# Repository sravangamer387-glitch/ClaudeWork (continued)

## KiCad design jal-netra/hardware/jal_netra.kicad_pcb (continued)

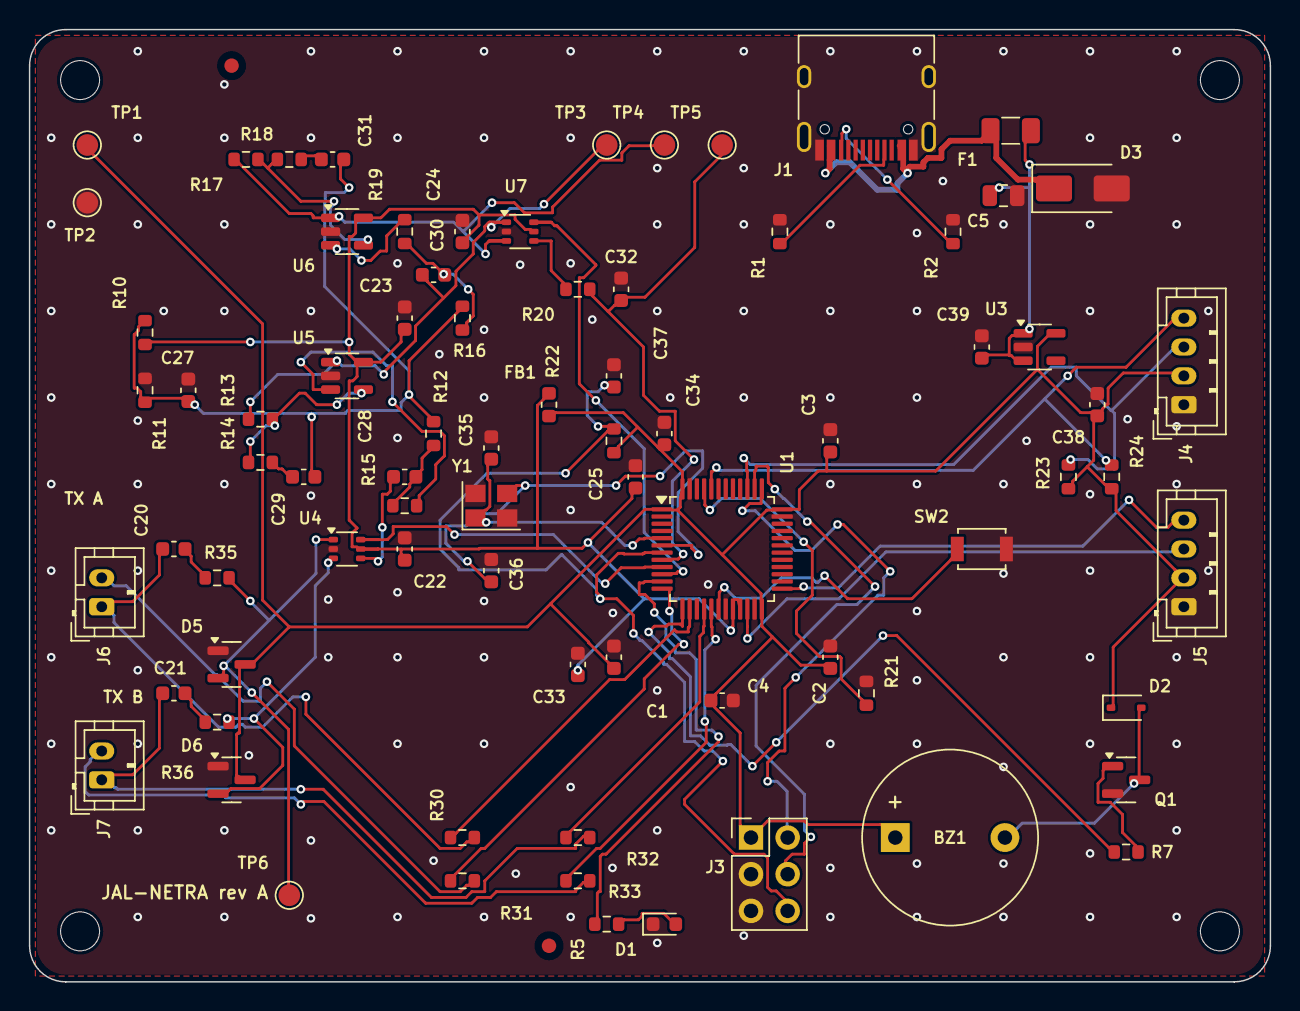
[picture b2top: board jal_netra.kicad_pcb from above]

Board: 2 copper layers, 86.0 x 66.0 mm, 84 parts (0 on the bottom side), 51 nets.

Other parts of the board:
FID1, FID2: Fiducial; Fiducial_1mm_Mask2mm
H1, H2, H3, H4: M2.5; MountingHole_2.7mm_M2.5

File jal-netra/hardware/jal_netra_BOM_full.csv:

Ref,Value,Footprint,Manufacturer part,LCSC #,LCSC status,Assembly
U1,STM32G431CBT6,Package_QFP:LQFP-48_7x7mm_P0.5mm,STM32G431CBT6,,,hand/THT
U4,TS5A3159,Package_TO_SOT_SMD:SOT-363_SC-70-6,,,,hand/THT
U5,OPA356,Package_TO_SOT_SMD:SOT-23-5,,,,hand/THT
U6,OPA356,Package_TO_SOT_SMD:SOT-23-5,,,,hand/THT
U7,TS5A3159,Package_TO_SOT_SMD:SOT-363_SC-70-6,,,,hand/THT
U3,AP2112K-3.3,Package_TO_SOT_SMD:SOT-23-5,,,,hand/THT
FB1,BLM18 600R,Inductor_SMD:L_0603_1608Metric,,,,hand/THT
Y1,8 MHz,Crystal:Crystal_SMD_3225-4Pin_3.2x2.5mm,,,,hand/THT
D5,BAV99,Package_TO_SOT_SMD:SOT-23,,,,hand/THT
D6,BAV99,Package_TO_SOT_SMD:SOT-23,,,,hand/THT
J6,Transducer A (BTL),Connector_JST:JST_PH_B2B-PH-K_1x02_P2.00mm_Vertical,,,,hand/THT
J7,Transducer B (BTL),Connector_JST:JST_PH_B2B-PH-K_1x02_P2.00mm_Vertical,,,,hand/THT
R30,22,Resistor_SMD:R_0603_1608Metric,,,,hand/THT
R31,22,Resistor_SMD:R_0603_1608Metric,,,,hand/THT
R32,22,Resistor_SMD:R_0603_1608Metric,,,,hand/THT
R33,22,Resistor_SMD:R_0603_1608Metric,,,,hand/THT
C20,10n,Capacitor_SMD:C_0603_1608Metric,0603 10nF X7R,C57112,verified,SMT (JLC)
R35,1k,Resistor_SMD:R_0603_1608Metric,0603 1k 1%,C21190,verified,SMT (JLC)
C21,10n,Capacitor_SMD:C_0603_1608Metric,0603 10nF X7R,C57112,verified,SMT (JLC)
R36,1k,Resistor_SMD:R_0603_1608Metric,0603 1k 1%,C21190,verified,SMT (JLC)
C22,100n,Capacitor_SMD:C_0603_1608Metric,0603 100nF X7R,C14663,verified,SMT (JLC)
C23,100n,Capacitor_SMD:C_0603_1608Metric,0603 100nF X7R,C14663,verified,SMT (JLC)
C24,100n,Capacitor_SMD:C_0603_1608Metric,0603 100nF X7R,C14663,verified,SMT (JLC)
C25,1u,Capacitor_SMD:C_0603_1608Metric,0603 1uF X7R,C15849,verified,SMT (JLC)
R10,10k,Resistor_SMD:R_0603_1608Metric,0603 10k 1%,C25804,verified,SMT (JLC)
R11,10k,Resistor_SMD:R_0603_1608Metric,0603 10k 1%,C25804,verified,SMT (JLC)
C27,1u,Capacitor_SMD:C_0603_1608Metric,0603 1uF X7R,C15849,verified,SMT (JLC)
C28,10n,Capacitor_SMD:C_0603_1608Metric,0603 10nF X7R,C57112,verified,SMT (JLC)
R12,100k,Resistor_SMD:R_0603_1608Metric,0603 100k 1%,C25803,verified,SMT (JLC)
R13,2.2k,Resistor_SMD:R_0603_1608Metric,0603 2.2k 1%,C4190,memory,SMT (JLC)
R14,240,Resistor_SMD:R_0603_1608Metric,,,,hand/THT
C29,1u,Capacitor_SMD:C_0603_1608Metric,0603 1uF X7R,C15849,verified,SMT (JLC)
R15,0,Resistor_SMD:R_0603_1608Metric,,,,hand/THT
C30,10n,Capacitor_SMD:C_0603_1608Metric,0603 10nF X7R,C57112,verified,SMT (JLC)
R16,100k,Resistor_SMD:R_0603_1608Metric,0603 100k 1%,C25803,verified,SMT (JLC)
R17,1k,Resistor_SMD:R_0603_1608Metric,0603 1k 1%,C21190,verified,SMT (JLC)
R18,100,Resistor_SMD:R_0603_1608Metric,,,,hand/THT
C31,1u,Capacitor_SMD:C_0603_1608Metric,0603 1uF X7R,C15849,verified,SMT (JLC)
R19,0,Resistor_SMD:R_0603_1608Metric,,,,hand/THT
R20,33,Resistor_SMD:R_0603_1608Metric,,,,hand/THT
C32,22p,Capacitor_SMD:C_0603_1608Metric,,,,hand/THT
C1,100n,Capacitor_SMD:C_0603_1608Metric,0603 100nF X7R,C14663,verified,SMT (JLC)
C2,100n,Capacitor_SMD:C_0603_1608Metric,0603 100nF X7R,C14663,verified,SMT (JLC)
C3,100n,Capacitor_SMD:C_0603_1608Metric,0603 100nF X7R,C14663,verified,SMT (JLC)
C4,100n,Capacitor_SMD:C_0603_1608Metric,0603 100nF X7R,C14663,verified,SMT (JLC)
C33,100n,Capacitor_SMD:C_0603_1608Metric,0603 100nF X7R,C14663,verified,SMT (JLC)
C34,4.7u,Capacitor_SMD:C_0603_1608Metric,,,,hand/THT
C35,15p,Capacitor_SMD:C_0603_1608Metric,,,,hand/THT
C36,15p,Capacitor_SMD:C_0603_1608Metric,,,,hand/THT
R21,10k,Resistor_SMD:R_0603_1608Metric,0603 10k 1%,C25804,verified,SMT (JLC)
R22,10k,Resistor_SMD:R_0603_1608Metric,0603 10k 1%,C25804,verified,SMT (JLC)
C37,100n,Capacitor_SMD:C_0603_1608Metric,0603 100nF X7R,C14663,verified,SMT (JLC)
C38,1u,Capacitor_SMD:C_0603_1608Metric,0603 1uF X7R,C15849,verified,SMT (JLC)
C39,1u,Capacitor_SMD:C_0603_1608Metric,0603 1uF X7R,C15849,verified,SMT (JLC)
J4,OLED I2C,Connector_JST:JST_PH_B4B-PH-K_1x04_P2.00mm_Vertical,,,,hand/THT
R23,4.7k,Resistor_SMD:R_0603_1608Metric,0603 4.7k 1%,C23162,memory,SMT (JLC)
R24,4.7k,Resistor_SMD:R_0603_1608Metric,0603 4.7k 1%,C23162,memory,SMT (JLC)
J5,UART host / BLE,Connector_JST:JST_PH_B4B-PH-K_1x04_P2.00mm_Vertical,,,,hand/THT
J3,SWD,Connector_PinHeader_2.54mm:PinHeader_2x03_P2.54mm_Vertical,,,,hand/THT
SW2,Test / zero,Button_Switch_SMD:SW_SPST_B3U-1000P,,,,hand/THT
TP1,TP,TestPoint:TestPoint_Pad_D1.5mm,,,,hand/THT
TP2,TP,TestPoint:TestPoint_Pad_D1.5mm,,,,hand/THT
TP3,TP,TestPoint:TestPoint_Pad_D1.5mm,,,,hand/THT
TP4,TP,TestPoint:TestPoint_Pad_D1.5mm,,,,hand/THT
TP5,TP,TestPoint:TestPoint_Pad_D1.5mm,,,,hand/THT
TP6,TP,TestPoint:TestPoint_Pad_D1.5mm,,,,hand/THT
J1,USB-C 5V,Connector_USB:USB_C_Receptacle_HRO_TYPE-C-31-M-12,TYPE-C-31-M-12,C165948,verified,SMT (JLC)
F1,PTC 500mA,Fuse:Fuse_1206_3216Metric,,,,hand/THT
D3,SMAJ5.0A,Diode_SMD:D_SMA,,,,hand/THT
R1,5.1k,Resistor_SMD:R_0603_1608Metric,0603 5.1k 1%,C23186,memory,SMT (JLC)
R2,5.1k,Resistor_SMD:R_0603_1608Metric,0603 5.1k 1%,C23186,memory,SMT (JLC)
C5,10u,Capacitor_SMD:C_0805_2012Metric,0805 10uF X5R,C15850,memory,SMT (JLC)
BZ1,Buzzer,Buzzer_Beeper:Buzzer_12x9.5RM7.6,,,,hand/THT
Q1,MMBT3904,Package_TO_SOT_SMD:SOT-23,MMBT3904,C20526,verified,SMT (JLC)
D2,1N4148WS,Diode_SMD:D_SOD-323,1N4148WS,C2128,verified,SMT (JLC)
R7,1k,Resistor_SMD:R_0603_1608Metric,0603 1k 1%,C21190,verified,SMT (JLC)
D1,Green,LED_SMD:LED_0603_1608Metric,,,,hand/THT
R5,1k,Resistor_SMD:R_0603_1608Metric,0603 1k 1%,C21190,verified,SMT (JLC)

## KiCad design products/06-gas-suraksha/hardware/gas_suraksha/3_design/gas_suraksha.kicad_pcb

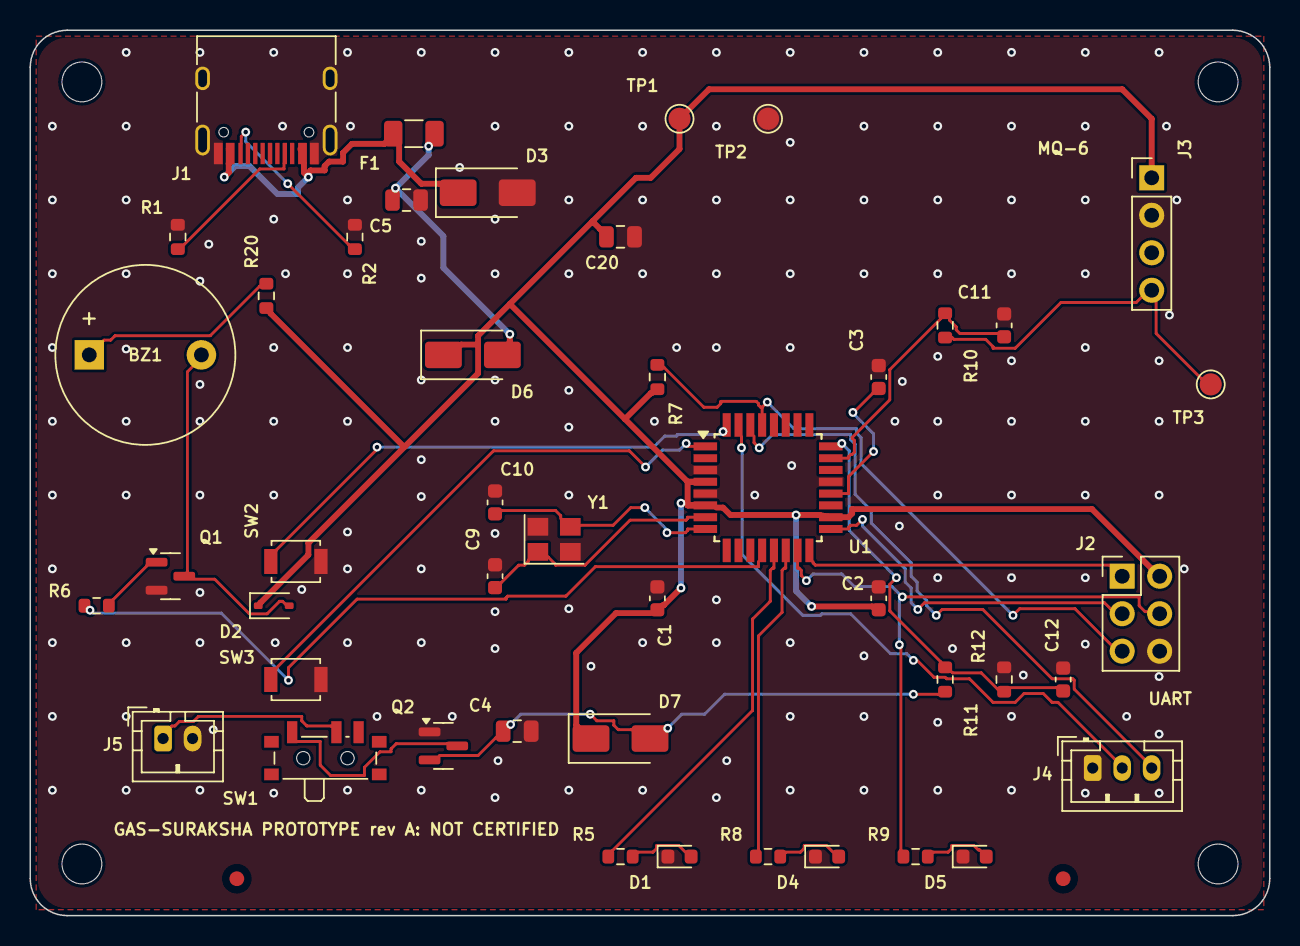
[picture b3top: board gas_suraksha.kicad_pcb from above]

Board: 2 copper layers, 84.0 x 60.0 mm, 51 parts (0 on the bottom side), 32 nets.

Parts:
BZ1: Buzzer active 3V; Buzzer_12x9.5RM7.6
C1, C2, C3, C11, C12: 100n; C_0603_1608Metric
C4, C5, C20: 10u; C_0805_2012Metric
C9, C10: 22p; C_0603_1608Metric
D1: Green; LED_0603_1608Metric
D2: 1N4148WS; D_SOD-323
D3: SMAJ5.0A; D_SMA
D4: Amber; LED_0603_1608Metric
D5: Red; LED_0603_1608Metric
D6, D7: SS14; D_SMA
F1: PTC 500mA; Fuse_1206_3216Metric
FID1, FID2: Fiducial; Fiducial_1mm_Mask2mm
H1, H2, H3, H4: M2.5; MountingHole_2.7mm_M2.5
J1: USB-C 5V; USB_C_Receptacle_HRO_TYPE-C-31-M-12
J2: ISP; PinHeader_2x03_P2.54mm_Vertical
J3: MQ-6 module: VCC GND DO AO; PinHeader_1x04_P2.54mm_Vertical
J4: UART log (adapter RX, TX); JST_PH_B3B-PH-K_1x03_P2.00mm_Vertical
J5: BATT 3xAA; JST_PH_B2B-PH-K_1x02_P2.00mm_Vertical
Q1: MMBT3904; SOT-23
Q2: AO3401A; SOT-23
R1, R2: 5.1k; R_0603_1608Metric
R5, R6, R8, R9, R10: 1k; R_0603_1608Metric
R7: 10k; R_0603_1608Metric
R11, R12: 220k; R_0603_1608Metric
R20: 47; R_0603_1608Metric
SW1: Power; SW_SPDT_PCM12
SW2: Silence; SW_SPST_B3U-1000P
SW3: Test; SW_SPST_B3U-1000P
TP1, TP2, TP3: TP; TestPoint_Pad_D1.5mm
U1: ATmega328P-AU; TQFP-32_7x7mm_P0.8mm
Y1: 16 MHz; Crystal_SMD_3225-4Pin_3.2x2.5mm

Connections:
+4V5: C4.1, D7.2, Q2.2, R11.1
+5V: C5.1, D6.2, F1.2
AREF: C3.1, U1.20
BATSENSE: C12.1, R11.2, R12.1, U1.24
BAT_P: J5.1, SW1.2
BAT_SW: Q2.3, SW1.1
BUZ: R6.1, U1.12
BUZ_B: Q1.1, R6.2
BZ_N: BZ1.2, D2.2, Q1.3
BZ_P: BZ1.1, R20.2
CC1: J1.A5, R1.1
CC2: J1.B5, R2.1
D1_A: D1.2, R5.2
D4_A: D4.2, R8.2
D5_A: D5.2, R9.2
GND: C1.2, C2.2, C3.2, C4.2, C5.2, C9.2, C10.2, C11.2, C12.2, C20.2, D1.1, D3.2, D4.1, D5.1, J1.A1, J1.A12, J1.B1, J1.B12, J1.S1, J2.6, J3.2, J4.1, J5.2, Q1.2, Q2.1, R1.2, R2.2, R12.2, SW2.2, SW3.2, TP2.1, U1.3, U1.5, U1.21, Y1.2, Y1.4
LED_A: R8.1, U1.14
LED_G: R5.1, U1.13
MISO: J2.1, U1.16
MOSI: J2.4, R9.1, U1.15
RESET: J2.5, R7.2, U1.29
RXD: J4.3, U1.30
SCK: J2.3, U1.17
SENSE: J3.4, R10.1, TP3.1
SENSE_F: C11.1, R10.2, U1.23
SILENCE: SW2.1, U1.32
TEST: SW3.1, U1.1
TXD: J4.2, U1.31
VBUS: D3.1, F1.1, J1.A4, J1.A9, J1.B4, J1.B9
VSYS: C1.1, C2.1, C20.1, D2.1, D6.1, D7.1, J2.2, J3.1, R7.1, R20.1, TP1.1, U1.4, U1.6, U1.18
XTAL1: C9.1, U1.7, Y1.1
XTAL2: C10.1, U1.8, Y1.3

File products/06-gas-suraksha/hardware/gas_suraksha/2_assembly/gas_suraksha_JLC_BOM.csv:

Comment,Designator,Footprint,LCSC Part #
USB-C 5V,J1,USB_C_Receptacle_HRO_TYPE-C-31-M-12,C165948
PTC 500mA,F1,Fuse_1206_3216Metric,C163512
SMAJ5.0A,D3,D_SMA,C83329
5.1k,"R1,R2",R_0603_1608Metric,C23186
10u,"C5,C4,C20",C_0805_2012Metric,C15850
Power,SW1,SW_SPDT_PCM12,C221841
AO3401A,Q2,SOT-23,C15127
MMBT3904,Q1,SOT-23,C20526
1N4148WS,D2,D_SOD-323,C2128
1k,"R6,R10,R5,R8,R9",R_0603_1608Metric,C21190
ATmega328P-AU,U1,TQFP-32_7x7mm_P0.8mm,C14877
100n,"C1,C2,C3,C11,C12",C_0603_1608Metric,C1591
10k,R7,R_0603_1608Metric,C25804
47,R20,R_0603_1608Metric,C23182
SS14,"D6,D7",D_SMA,C84343
16 MHz,Y1,Crystal_SMD_3225-4Pin_3.2x2.5mm,C12668
22p,"C9,C10",C_0603_1608Metric,C1653
220k,"R11,R12",R_0603_1608Metric,C22961
Silence,SW2,SW_SPST_B3U-1000P,C231329
Test,SW3,SW_SPST_B3U-1000P,C231329
Green,D1,LED_0603_1608Metric,C2289
Amber,D4,LED_0603_1608Metric,C2287
Red,D5,LED_0603_1608Metric,C2286

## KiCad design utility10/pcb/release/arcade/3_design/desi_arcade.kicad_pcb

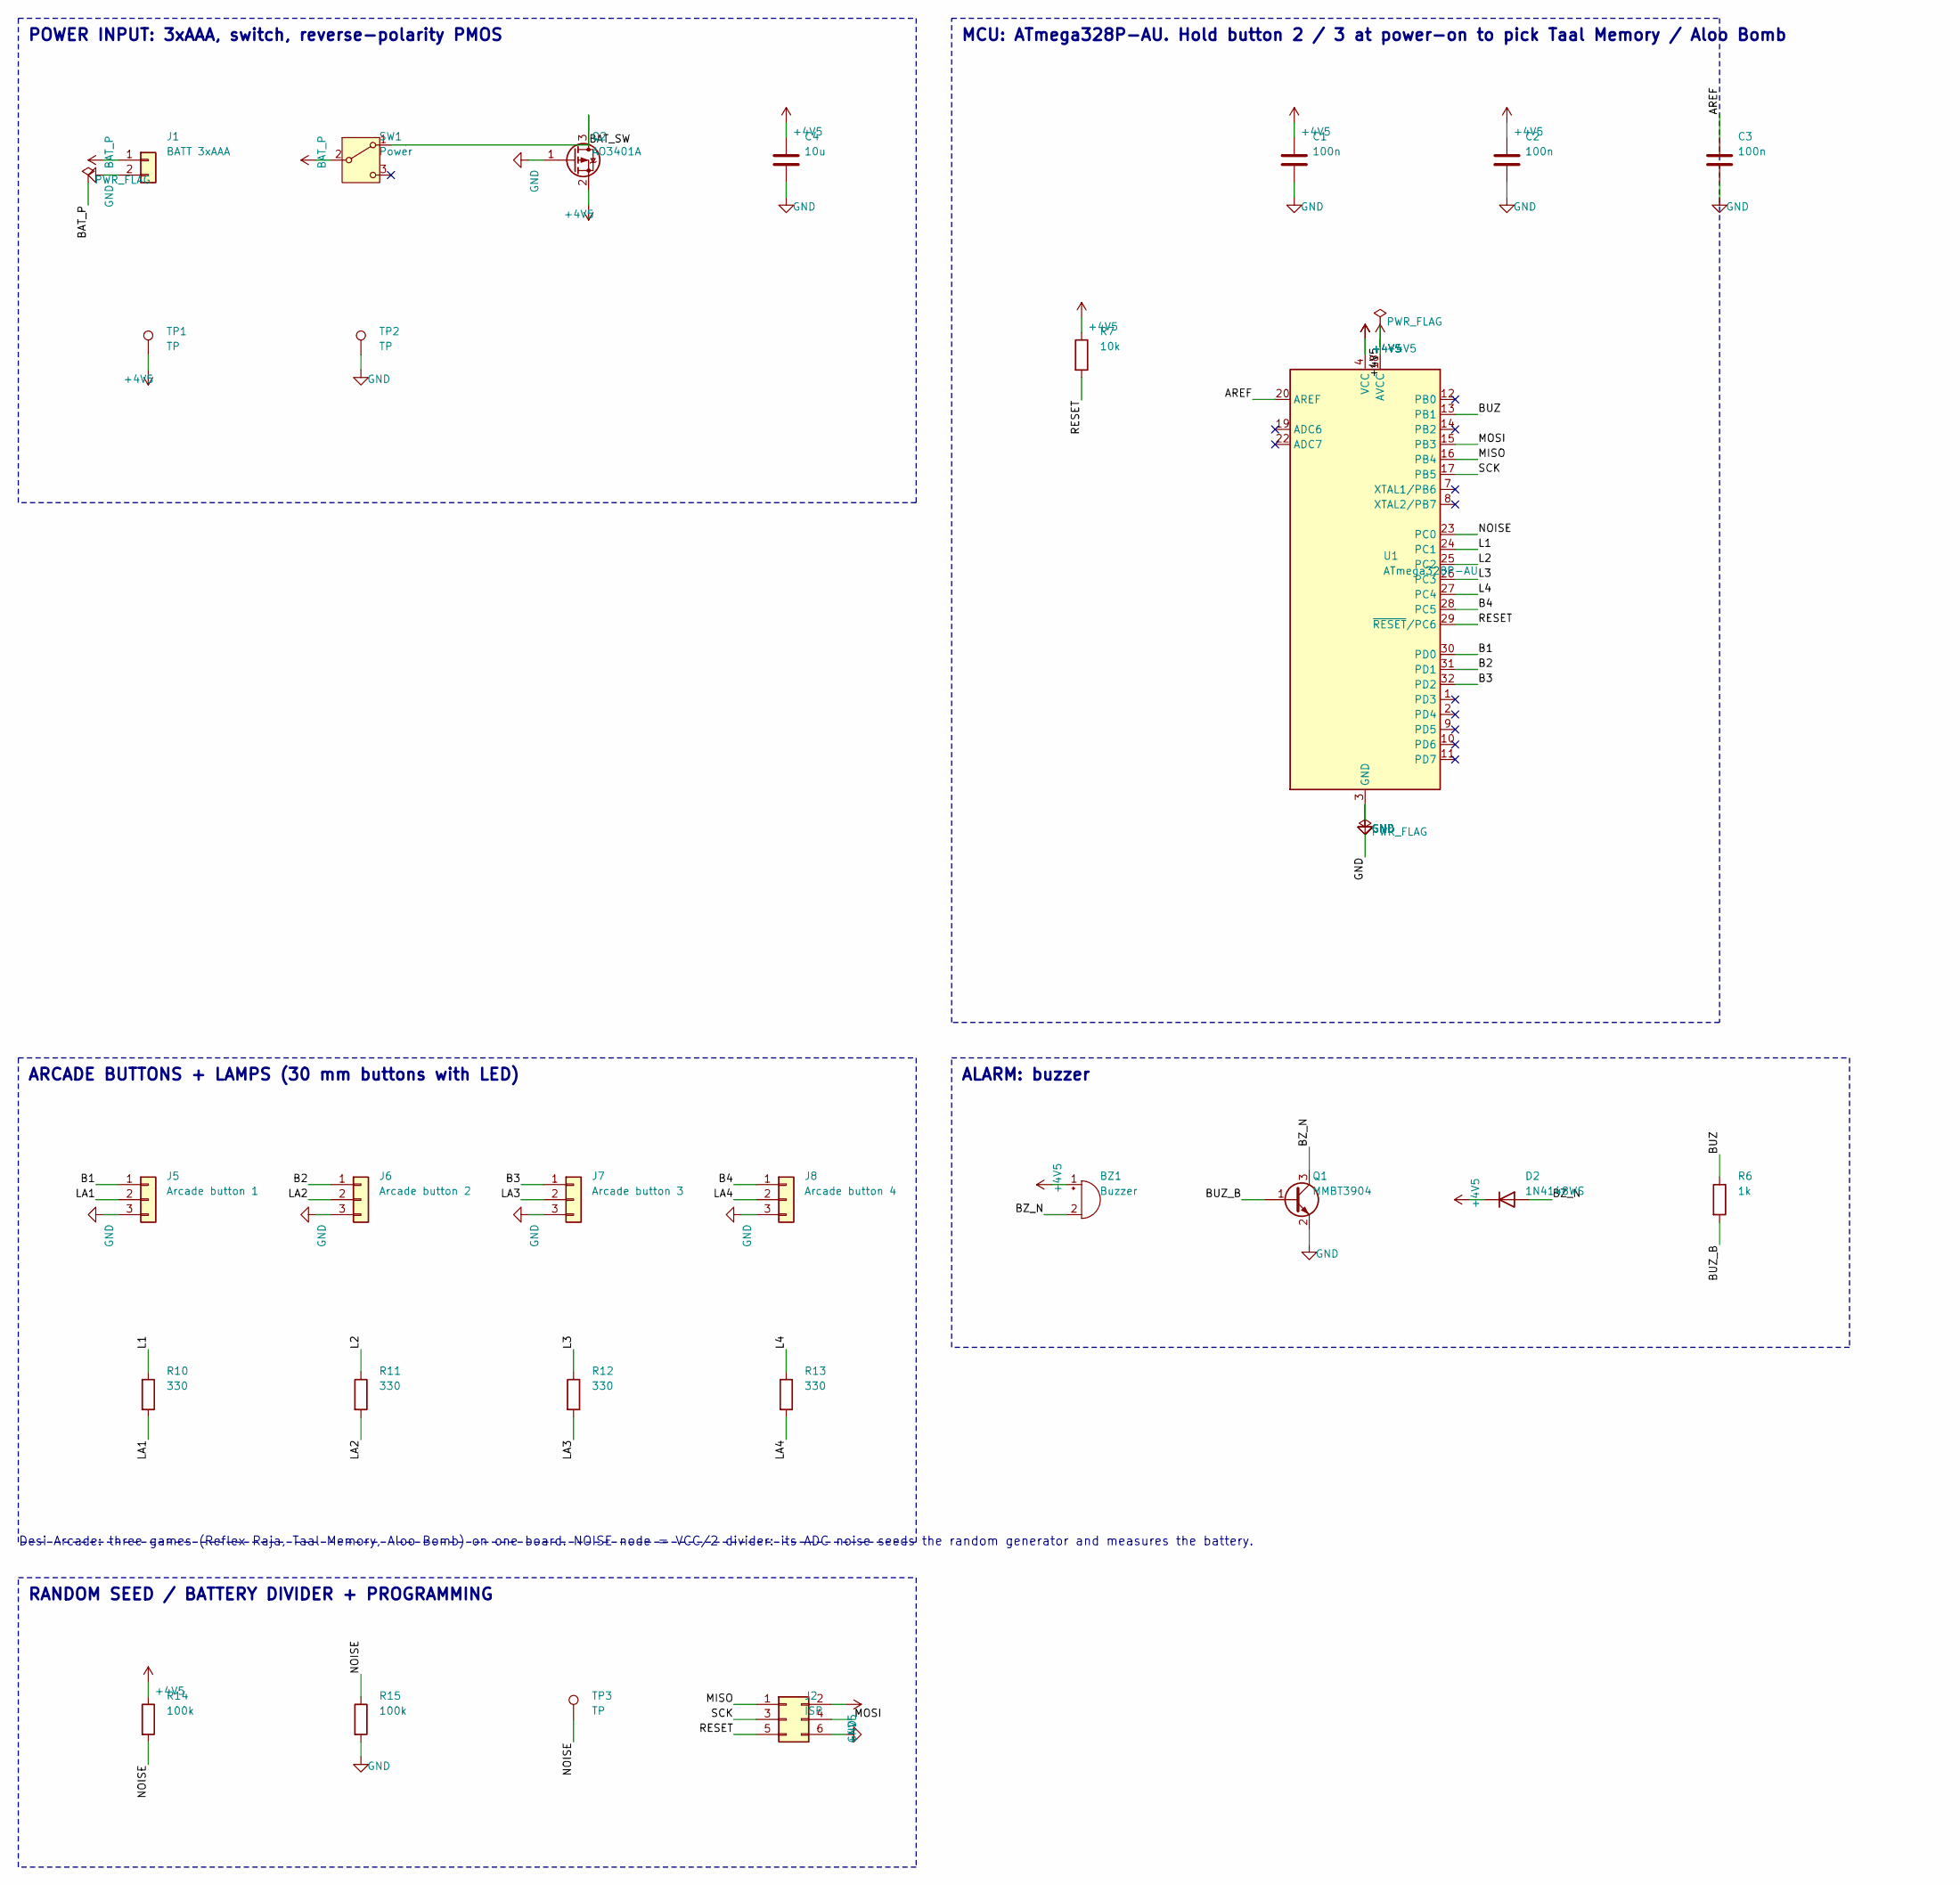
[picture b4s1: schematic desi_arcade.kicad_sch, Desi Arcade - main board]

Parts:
BZ1: Buzzer; Buzzer_12x9.5RM7.6
C1, C2, C3: 100n; C_0603_1608Metric
C4: 10u; C_0805_2012Metric
D2: 1N4148WS; D_SOD-323
J1: BATT 3xAAA; JST_PH_B2B-PH-K_1x02_P2.00mm_Vertical
J2: ISP; PinHeader_2x03_P2.54mm_Vertical
J5: Arcade button 1; JST_PH_B3B-PH-K_1x03_P2.00mm_Vertical
J6: Arcade button 2; JST_PH_B3B-PH-K_1x03_P2.00mm_Vertical
J7: Arcade button 3; JST_PH_B3B-PH-K_1x03_P2.00mm_Vertical
J8: Arcade button 4; JST_PH_B3B-PH-K_1x03_P2.00mm_Vertical
Q1: MMBT3904; SOT-23
Q2: AO3401A; SOT-23
R6: 1k; R_0603_1608Metric
R7: 10k; R_0603_1608Metric
R10, R11, R12, R13: 330; R_0603_1608Metric
R14, R15: 100k; R_0603_1608Metric
SW1: Power; SW_SPDT_PCM12
TP1, TP2, TP3: TP; TestPoint_Pad_D1.5mm
U1: ATmega328P-AU; TQFP-32_7x7mm_P0.8mm

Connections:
+4V5: BZ1.1 (+), C1.1, C2.1, C4.1, D2.1 (K), J2.2, Q2.2 (S), R7.1, R14.1, TP1.1, U1.4 (VCC), U1.6 (VCC), U1.18 (AVCC)
AREF: C3.1, U1.20 (AREF)
B1: J5.1, U1.30 (PD0)
B2: J6.1, U1.31 (PD1)
B3: J7.1, U1.32 (PD2)
B4: J8.1, U1.28 (PC5)
BAT_P: J1.1, SW1.2 (B)
BAT_SW: Q2.3 (D), SW1.1 (A)
BUZ: R6.1, U1.13 (PB1)
BUZ_B: Q1.1 (B), R6.2
BZ_N: BZ1.2 (-), D2.2 (A), Q1.3 (C)
GND: C1.2, C2.2, C3.2, C4.2, J1.2, J2.6, J5.3, J6.3, J7.3, J8.3, Q1.2 (E), Q2.1 (G), R15.2, TP2.1, U1.3 (GND), U1.5 (GND), U1.21 (GND)
L1: R10.1, U1.24 (PC1)
L2: R11.1, U1.25 (PC2)
L3: R12.1, U1.26 (PC3)
L4: R13.1, U1.27 (PC4)
LA1: J5.2, R10.2
LA2: J6.2, R11.2
LA3: J7.2, R12.2
LA4: J8.2, R13.2
MISO: J2.1, U1.16 (PB4)
MOSI: J2.4, U1.15 (PB3)
NOISE: R14.2, R15.1, TP3.1, U1.23 (PC0)
RESET: J2.5, R7.2, U1.29 (~RESET/PC6)
SCK: J2.3, U1.17 (PB5)

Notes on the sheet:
POWER INPUT: 3xAAA, switch, reverse-polarity PMOS
MCU: ATmega328P-AU. Hold button 2 / 3 at power-on to pick Taal Memory / Aloo Bomb
ARCADE BUTTONS + LAMPS (30 mm buttons with LED)
ALARM: buzzer
RANDOM SEED / BATTERY DIVIDER + PROGRAMMING
Desi Arcade: three games (Reflex Raja, Taal Memory, Aloo Bomb) on one board. NOISE node = VCC/2 divider: its ADC noise seeds the random generator and measures the battery.

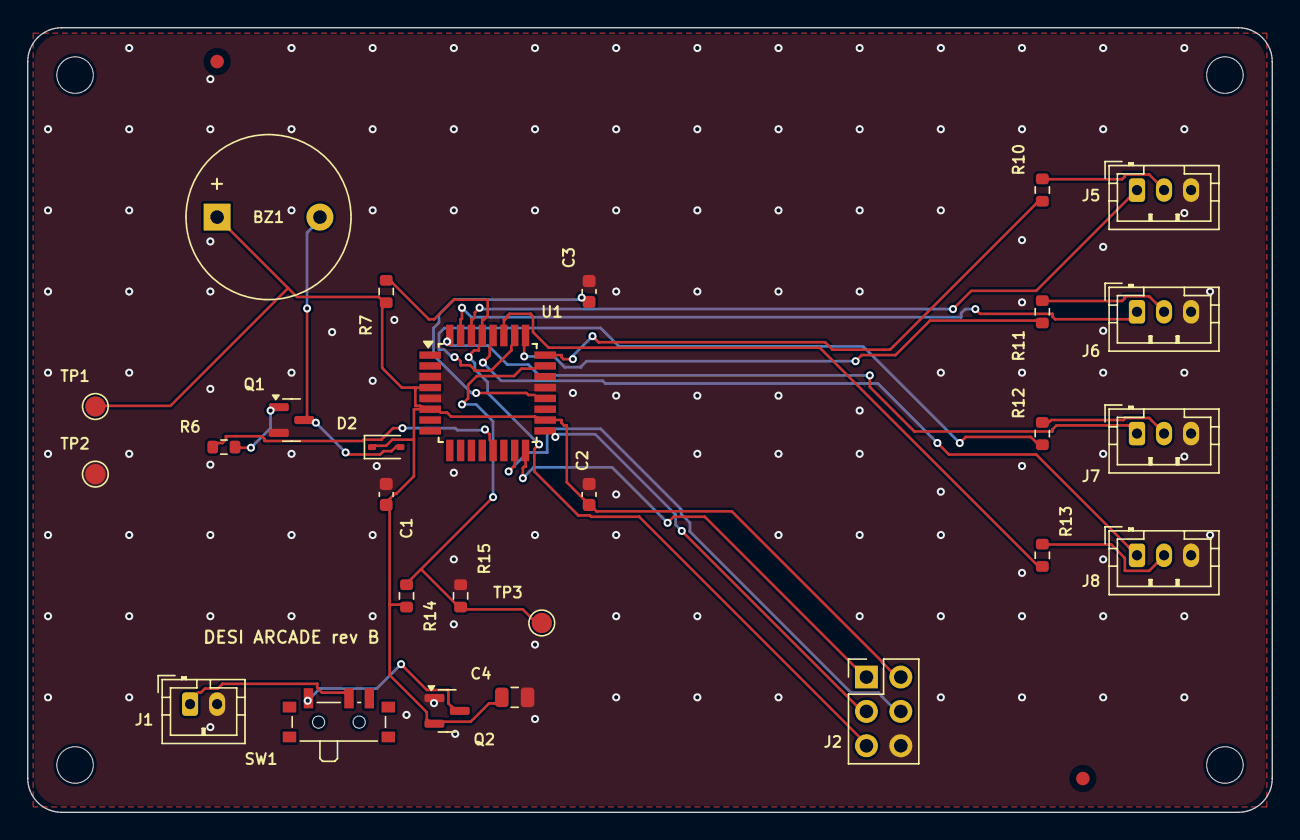
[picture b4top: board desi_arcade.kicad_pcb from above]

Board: 2 copper layers, 92.0 x 58.0 mm, 33 parts (0 on the bottom side), 25 nets.

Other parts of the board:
FID1, FID2: Fiducial; Fiducial_1mm_Mask2mm
H1, H2, H3, H4: M2.5; MountingHole_2.7mm_M2.5

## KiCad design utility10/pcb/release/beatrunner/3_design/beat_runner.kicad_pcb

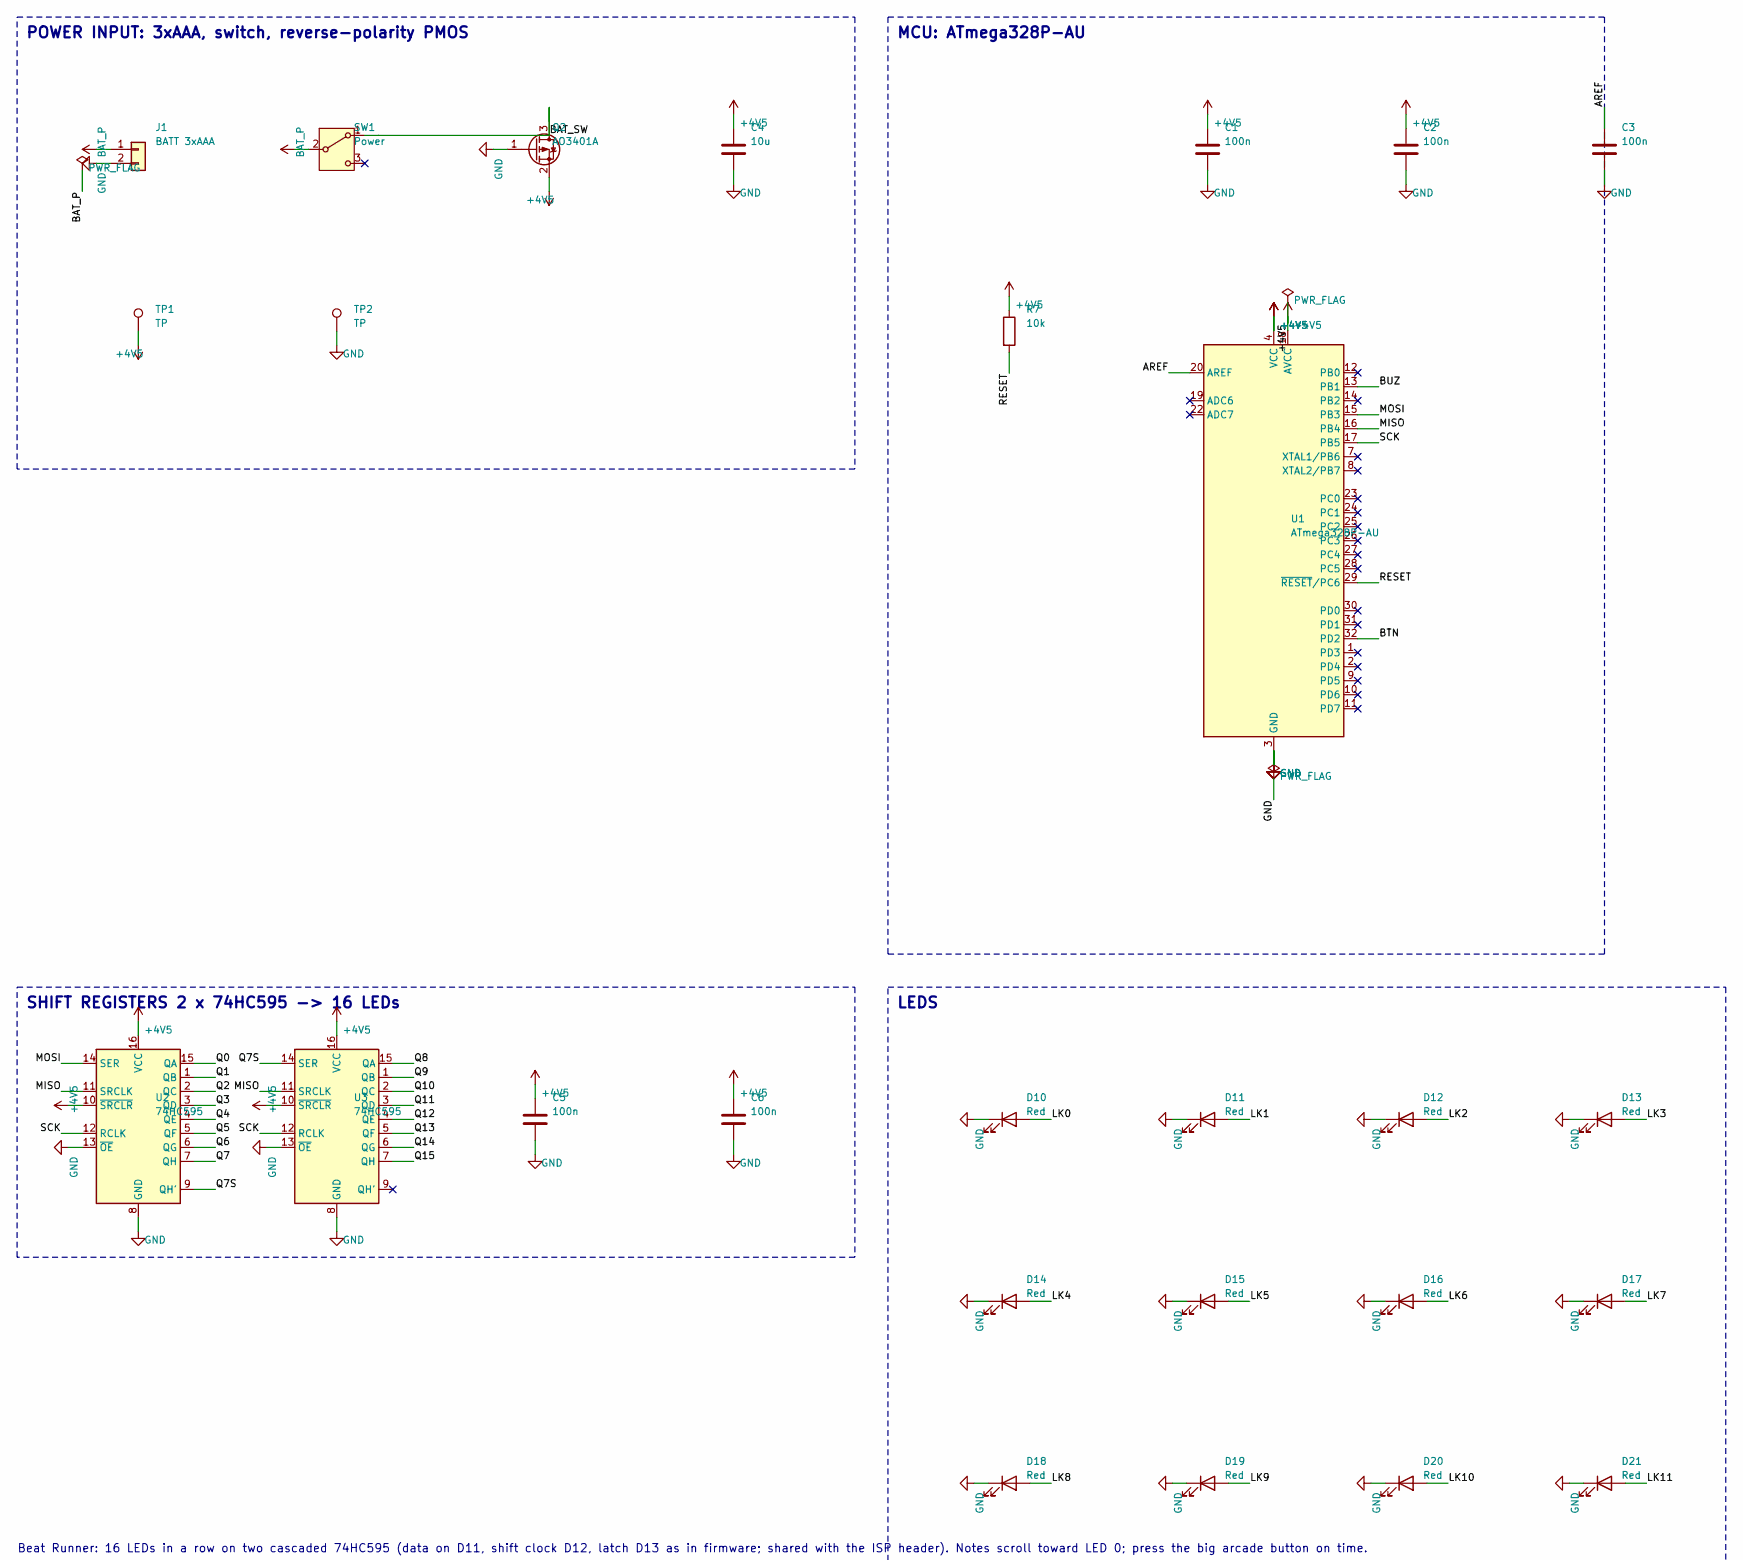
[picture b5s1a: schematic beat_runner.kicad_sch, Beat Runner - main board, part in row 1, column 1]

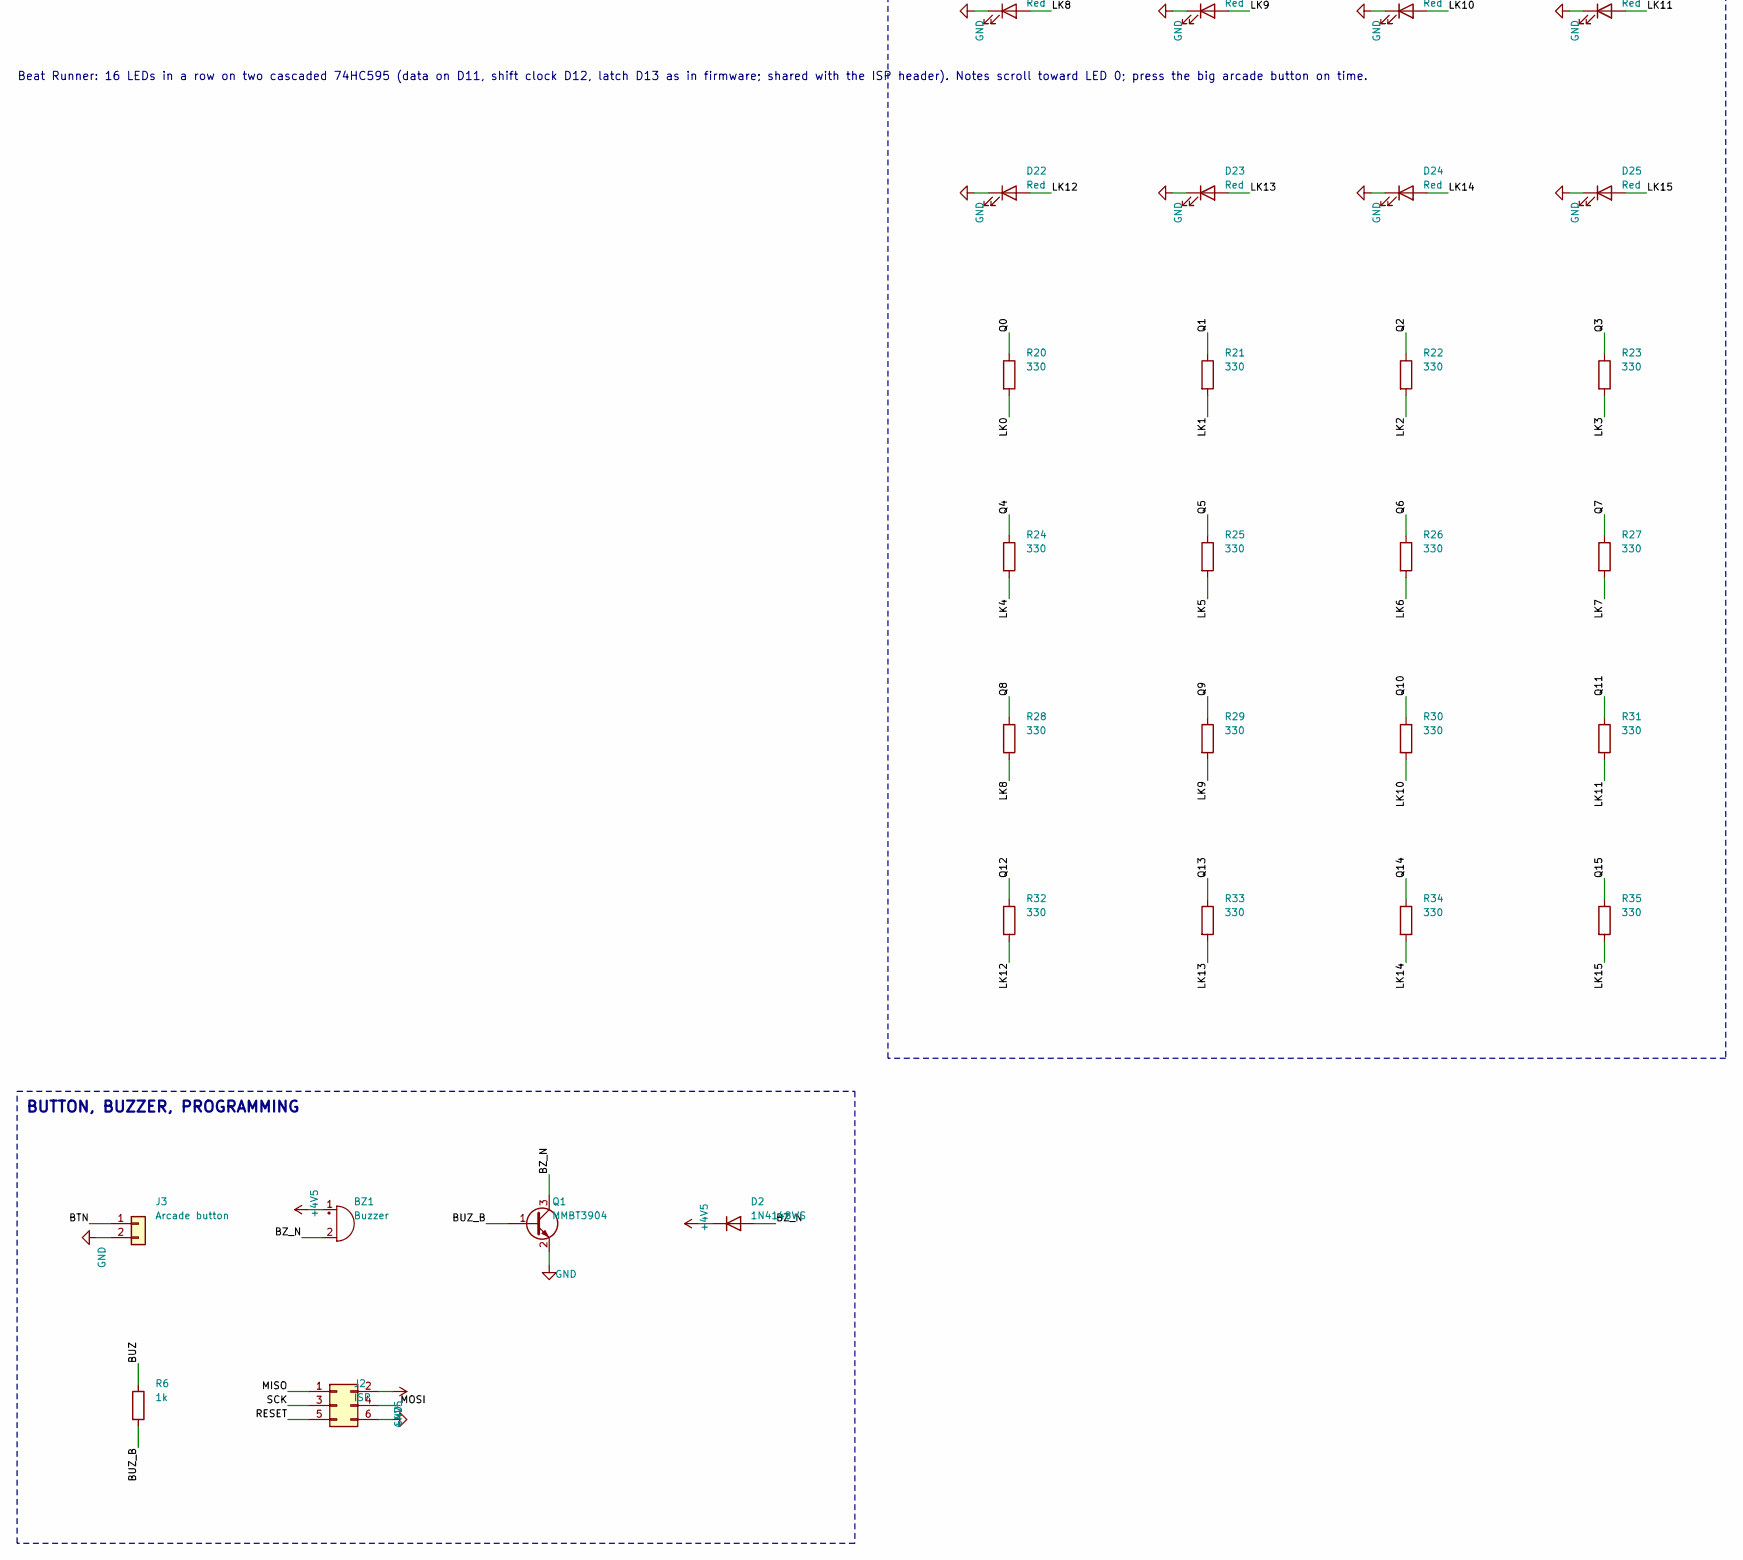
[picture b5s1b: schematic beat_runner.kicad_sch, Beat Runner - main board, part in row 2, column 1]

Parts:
BZ1: Buzzer; Buzzer_12x9.5RM7.6
C1, C2, C3, C5, C6: 100n; C_0603_1608Metric
C4: 10u; C_0805_2012Metric
D2: 1N4148WS; D_SOD-323
D10, D11, D12, D13, D14, D15, D16, D17, D18, D19, D20, D21, D22, D23, D24, D25: Red; LED_0603_1608Metric
J1: BATT 3xAAA; JST_PH_B2B-PH-K_1x02_P2.00mm_Vertical
J2: ISP; PinHeader_2x03_P2.54mm_Vertical
J3: Arcade button; JST_PH_B2B-PH-K_1x02_P2.00mm_Vertical
Q1: MMBT3904; SOT-23
Q2: AO3401A; SOT-23
R6: 1k; R_0603_1608Metric
R7: 10k; R_0603_1608Metric
R20, R21, R22, R23, R24, R25, R26, R27, R28, R29, R30, R31, R32, R33, R34, R35: 330; R_0603_1608Metric
SW1: Power; SW_SPDT_PCM12
TP1, TP2: TP; TestPoint_Pad_D1.5mm
U1: ATmega328P-AU; TQFP-32_7x7mm_P0.8mm
U2, U3: 74HC595; SOIC-16_3.9x9.9mm_P1.27mm

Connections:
+4V5: BZ1.1 (+), C1.1, C2.1, C4.1, C5.1, C6.1, D2.1 (K), J2.2, Q2.2 (S), R7.1, TP1.1, U1.4 (VCC), U1.6 (VCC), U1.18 (AVCC), U2.10 (~SRCLR), U2.16 (VCC), U3.10 (~SRCLR), U3.16 (VCC)
AREF: C3.1, U1.20 (AREF)
BAT_P: J1.1, SW1.2 (B)
BAT_SW: Q2.3 (D), SW1.1 (A)
BTN: J3.1, U1.32 (PD2)
BUZ: R6.1, U1.13 (PB1)
BUZ_B: Q1.1 (B), R6.2
BZ_N: BZ1.2 (-), D2.2 (A), Q1.3 (C)
GND: C1.2, C2.2, C3.2, C4.2, C5.2, C6.2, D10.1 (K), D11.1 (K), D12.1 (K), D13.1 (K), D14.1 (K), D15.1 (K), D16.1 (K), D17.1 (K), D18.1 (K), D19.1 (K), D20.1 (K), D21.1 (K), D22.1 (K), D23.1 (K), D24.1 (K), D25.1 (K), J1.2, J2.6, J3.2, Q1.2 (E), Q2.1 (G), TP2.1, U1.3 (GND), U1.5 (GND), U1.21 (GND), U2.8 (GND), U2.13 (~OE), U3.8 (GND), U3.13 (~OE)
LK0: D10.2 (A), R20.2
LK1: D11.2 (A), R21.2
LK2: D12.2 (A), R22.2
LK3: D13.2 (A), R23.2
LK4: D14.2 (A), R24.2
LK5: D15.2 (A), R25.2
LK6: D16.2 (A), R26.2
LK7: D17.2 (A), R27.2
LK8: D18.2 (A), R28.2
LK9: D19.2 (A), R29.2
LK10: D20.2 (A), R30.2
LK11: D21.2 (A), R31.2
LK12: D22.2 (A), R32.2
LK13: D23.2 (A), R33.2
LK14: D24.2 (A), R34.2
LK15: D25.2 (A), R35.2
MISO: J2.1, U1.16 (PB4), U2.11 (SRCLK), U3.11 (SRCLK)
MOSI: J2.4, U1.15 (PB3), U2.14 (SER)
Q0: R20.1, U2.15 (QA)
Q1: R21.1, U2.1 (QB)
Q2: R22.1, U2.2 (QC)
Q3: R23.1, U2.3 (QD)
Q4: R24.1, U2.4 (QE)
Q5: R25.1, U2.5 (QF)
Q6: R26.1, U2.6 (QG)
Q7: R27.1, U2.7 (QH)
Q7S: U2.9 (QH'), U3.14 (SER)
Q8: R28.1, U3.15 (QA)
Q9: R29.1, U3.1 (QB)
Q10: R30.1, U3.2 (QC)
Q11: R31.1, U3.3 (QD)
Q12: R32.1, U3.4 (QE)
Q13: R33.1, U3.5 (QF)
Q14: R34.1, U3.6 (QG)
Q15: R35.1, U3.7 (QH)
RESET: J2.5, R7.2, U1.29 (~RESET/PC6)
SCK: J2.3, U1.17 (PB5), U2.12 (RCLK), U3.12 (RCLK)

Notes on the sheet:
POWER INPUT: 3xAAA, switch, reverse-polarity PMOS
MCU: ATmega328P-AU
SHIFT REGISTERS 2 x 74HC595 -> 16 LEDs
LEDS
BUTTON, BUZZER, PROGRAMMING
Beat Runner: 16 LEDs in a row on two cascaded 74HC595 (data on D11, shift clock D12, latch D13 as in firmware; shared with the ISP header). Notes scroll toward LED 0; press the big arcade button on time.

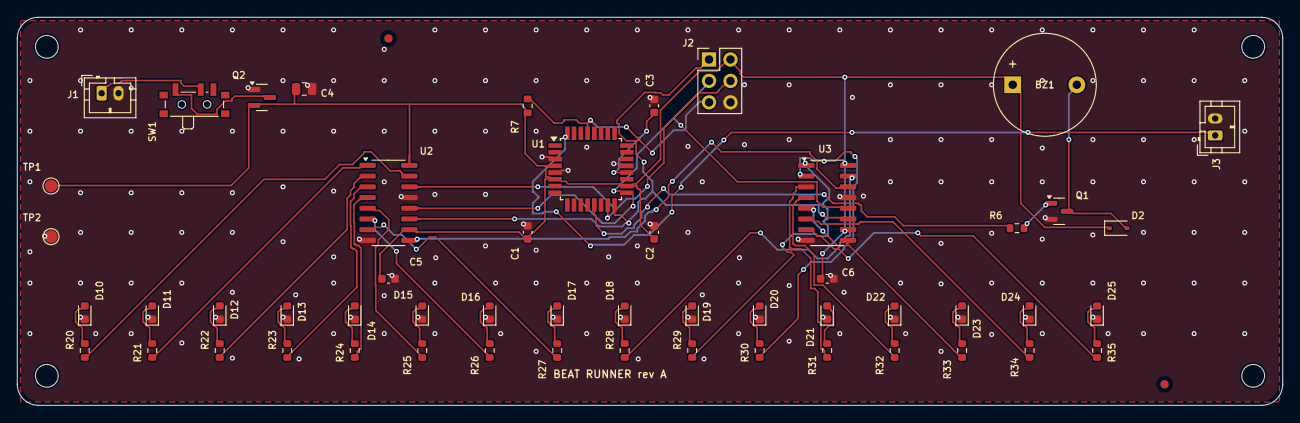
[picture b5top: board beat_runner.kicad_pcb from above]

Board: 2 copper layers, 150.0 x 46.0 mm, 59 parts (0 on the bottom side), 46 nets.

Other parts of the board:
FID1, FID2: Fiducial; Fiducial_1mm_Mask2mm
H1, H2, H3, H4: M2.5; MountingHole_2.7mm_M2.5
